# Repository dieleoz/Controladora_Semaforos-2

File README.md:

# 🚦 Controladora de Semáforos Móviles de 3 Estados (V9.1)

> 🧭 **Las decisiones vigentes viven en [`DECISIONES.md`](DECISIONES.md)** — una fila por
> decision, con su fecha, su motivo y que deroga. *(Aqui se publicaba cuantas hay; se quito el
> 11/09 porque decia 18 y 9 cuando ya eran mas: se cuentan alli.)* Si un parrafo de cualquier
> documento contradice una fila de ahi, **gana la fila**: el parrafo esta caducado. Se lee
> ANTES de encargar un cambio de alcance.

---

## 🔴 Lo que este README no puede decirte, y es lo primero

> ▶️ **Donde esta parado el trabajo y por donde se retoma lo dice [`ESTADO.md`](ESTADO.md)**, que se
> reescribe en cada cierre; aqui no se repite. Lo que paso, en [`HISTORIA.md`](HISTORIA.md) y en `git log`.

**La instalación certificada es `e303485` (V8.4, 31/07/2026).** Lo de debajo llegó a una mesa
el 3-4/09 y la noche del 04/09 —banco con dos tarjetas; la última cinta, 05/09 22:19, sobre
`42a52cd`— y 🔴 **el 10/09 llegó por primera vez a una calle: un Maestro (`SERIE:179DB0`)
corrió en El Sisga con firmware V9 `SIN_BANCO`** —el paquete del 08/09 (`7ff7d12`); después
se probó el del 10/09 (`b354fe9`)—. Su cinta y su diario están en `evidencia/` (308 tramas,
308 checksums que casan). Lo que se reportó allí, lo que dice la cinta y la rama que salió de
ahí, validada por el diff, están en `roadmap.md` §3.16 (`N-162`). 🔴 **Con `7ff7d12`, el
Maestro 179DB0 se declara en hora con el reloj parado: no se usa el Modo Degradado allí.**
**Desde el 29/09 el funcional prueba en banco las candidatas** (`a505fa2`, `6bd1e4f`, `d3606be`; cintas en
`evidencia/300920261130/`, `011020260934/`, `021020260914/`), **pero ninguna ha pasado banco completo.**

**La razon lineas de instrumento / lineas de producto la mide el pre-commit en cada commit**
(`.githooks/trinquete.sh`, contra el techo `RAZON_TECHO` de `.topes`): si sube por encima del techo, el
commit se para. El techo solo baja, cuando un acta de campo archiva un tema (`CLAUDE.md` §4). Cuenta
el indice, sin `historico/`, e incluye la app y el ESP32, asi que no se compara con las razones de la
serie anterior (esa serie, en [`HISTORIA.md`](HISTORIA.md)).

**Tres auditorías externas independientes dijeron lo mismo**, y la tercera lo dijo de la
respuesta a la segunda. La regla que salió de ahí vive en `CLAUDE.md` §0 y §8:

> **Un `20/20` sobre decenas de miles de líneas de instrumento que nunca han tocado una tarjeta
> no es un entregable: es una coartada.**

La tabla de abajo es verdad. **Lee lo que mide antes de lo que puntúa.**

---

## 📐 LA SPEC — empieza por aquí, y son nueve ficheros (`SPEC_0` a `SPEC_8`)

**Escritas el 12–13/09 desde el fuente, verificando cada afirmación contra el código; manda la SPEC y
`DECISIONES.md` es su índice.** `SPEC_0` es la vista del sistema y `SPEC_7` el modo sin reloj. Sustituyen a ~17.000
líneas de manuales que describían un sistema que ha cambiado cuatro veces.
**Nacieron por debajo de 300 líneas a propósito** (hoy `SPEC_1` y `SPEC_2` lo pasan): un fichero que no se puede leer
entero no lo lee nadie entero, y
entonces cada lector deriva su propia versión.

| | qué contesta |
|---|---|
| [`SPEC_0_El_Sistema`](05_Funcional/SPEC_0_El_Sistema.md) | la vista del sistema: qué es, cómo se pone un cruce a funcionar y lo que el equipo no hace (§5) |
| [`SPEC_7_Modo_Sin_Reloj`](05_Funcional/SPEC_7_Modo_Sin_Reloj.md) | el modo sin reloj y sin radio: el veredicto es que **no se construye** |
| [`SPEC_1_Ciclo_y_Luces`](05_Funcional/SPEC_1_Ciclo_y_Luces.md) | qué hace **un** poste con sus tres luces y su pluma: modos, tiempos, transiciones, la barrera de salidas |
| [`SPEC_2_Dos_Puntas_y_Radio`](05_Funcional/SPEC_2_Dos_Puntas_y_Radio.md) | 🔴 **lo único de verdad difícil: que los dos postes NUNCA den verde a la vez**, con una radio lenta que pierde tramas y sin cable entre ellos; y sin radio, el Degradado con testigo (§7.bis) y el **automatico a eleccion del tecnico** (§7.ter, 29/09) |
| [`SPEC_3_La_Hora`](05_Funcional/SPEC_3_La_Hora.md) | de dónde sale la hora y qué pasa cuando se pierde — **es lo que autoriza el Degradado**, o sea el modo que da verdes sin confirmar con la otra punta |
| [`SPEC_4_App_y_Bluetooth`](05_Funcional/SPEC_4_App_y_Bluetooth.md) | la **única** forma de operar el equipo (`D-16`): qué órdenes hay, qué contesta el equipo a cada una y de qué depende esa respuesta |
| [`SPEC_5_Cobre_Camaras_Pluma`](05_Funcional/SPEC_5_Cobre_Camaras_Pluma.md) | 🛑 **qué hay en cada pin, qué es peligroso y qué no se ha medido nunca.** Se lee con un destornillador en la mano |
| [`SPEC_8_Camaras_y_Barrera`](05_Funcional/SPEC_8_Camaras_y_Barrera.md) | 🛑 **qué HACE el equipo con las cámaras y la barrera**: el veto, el retardo de 3 s, cuándo pide que se revise una cámara, los dos interruptores de administrador, y **qué NO protege**. Es la otra mitad de `SPEC_5`: aquí lo que decide el **firmware**, allí lo que decide el **cobre** |
| [`SPEC_6_Campo_Radio_y_Alarmas`](05_Funcional/SPEC_6_Campo_Radio_y_Alarmas.md) | el **procedimiento de campo** del Degradado, la configuración de radio y antenas, y la tabla completa de alarmas → qué hace el técnico |

> ⚠️ **La spec dice qué HACE el equipo hoy, no qué debería hacer.** Lo que no cumple una decisión vigente vive
> en el apartado «HUECOS MEDIDOS» de cada una, con la medida pegada. **Y los manuales viejos siguen en el
> árbol a propósito**: se intentó jubilarlos y se paró con medida — hay contenido que ninguna spec cubre
> todavía (la receta de la APK, los ensayos de cámara con instrumento, la trama canónica con checksums de la
> que cuelga un pack). Está contado en `roadmap.md` 1.35(a).

## 🔧 Qué se probó en banco, y qué no

> **El 3 y 4 de Septiembre esto vio una tarjeta.** El funcional ejecutó la guía de 29 pasos
> sobre `617bd00`: **24 pasos completados**, 4 bloqueados por el enlace Bluetooth y 1 abortado
> por un incidente de seguridad. Informe en
> `evidencia/Informe_Pruebas_Banco_Semaforos_V9.0.pdf`.
>
> **Funcionó en cobre:** carga por SWD al primer intento, radio entre puntas con caída a ámbar
> en ~20 s y vuelta sola en ~3 s, talanquera, cámara de demanda y masa común a 0 V.
>
> ✅ **La regresión N-42 —el Modo Automático no movía las luces— está CERRADA EN COBRE.** La
> cerró la sesión de banco de la noche del 04/09, con el responsable delante: *«ahí cambia ese
> amarillo y este a verde. Ahora está funcionando»*. El arreglo es `ceb8cc5` —se retiró el
> asistente entero: una sola puerta, el modo arranca corriendo—. *(Este README publicó
> «regresión abierta» hasta el 07/09; el banco la había cerrado tres días antes.)*
>
> 🔴 **Y aparecieron tres defectos que ninguna cifra de la tabla de abajo podía ver**, porque
> ninguno es una propiedad del código: la tarjeta Maestro tiene un corto de 3,3 V a masa
> (**N-116**), las entradas de campo no tienen ninguna protección mientras las salidas sí
> (**N-120**), y el ESP32 no se anunciaba por Bluetooth (**N-117**). **Los tres pasaron el
> `20/20` sin despeinarlo.**
>
> *(El cuarto de aquella lista, **N-118** —«el mando A/B no responde, 0,6 V en reposo»—, quedó
> **REFUTADO el 05/09**: el propio banco había medido las dos ramas del experimento en la misma
> tabla. Mismo cobre, distinto `pinMode`, distinta tensión. Ver `05_Funcional/historico/DECISIONES_hist.md`, cerradas.)*

**Verificación actual** — cifras **copiadas del acta**
[`evidencia/2026-11-10_compuerta.txt`](evidencia/2026-11-10_compuerta.txt), que genera
`python 01_Firmware/compuerta.py` en una sola corrida. No se escriben a mano — y desde **N-62**
eso ya no es una promesa: el pack `documentos_01_cifras_del_acta` compara esta tabla contra la
última acta en cada corrida del banco. Cuando se escribió por primera vez, **falló**: esta tabla
publicaba 32 rutas y 86,4 % de flash cuando el acta que ella misma citaba medía 38 rutas y
92,8 %. Las cifras eran del 05/08 y llevaban la palabra *«copiadas»* encima.

| Comprobación | Estado | |
|---|---|---|
| guarda de rutas de los instrumentos | ✅ | 72 rutas parseadas, todas existen |
| banco por packs *(70 packs)* | 🔴 **FALLA** | **1524/1525 comprobaciones en 70 packs** — 69 PASS, **1 FALLA**. `decisiones_01_anclas` acusa a **`D-22`** (necesita una tarjeta delante); no se decora (`CLAUDE.md` §1) |
| compila Maestro / Esclavo / ESP32 | ✅ | **85.5 %** · 72.3 % · 35.8 % — *el Maestro ocupa **53420 de 62464 B** (las tres ultimas paginas quedan para la instalacion de camaras y barrera, `D-165`, las franjas de noche, `D-108`, y el testigo de `D-35`); el Esclavo, **43964 B**. Subio con los parametros de instalacion (`N-187`). Bajo al quitar la libreria RTC (`N-172`) y subio con la salida programada (`D-52`) y el verde del testigo (`D-59`)* |
| simulador funcional | ✅ | 9/9 — eran 20, y 11 de aquellas no medían nada: se retiraron una a una con su evidencia |
| compila ESP32 | ✅ | 35.8 % — 1126409 de 3.145.728 B |
| simulador del puente ESP32 | ✅ | **159/159** — las tres puntas: `bluetooth.cpp` compilado, la app en jsdom, y solo el ESP32 modelado |
| simulador de app y bluetooth | ✅ | **12/12** — estuvo en `ABORTADO` unas horas el 05/09: **N-149** le añadió el campo `ESC` al `$STATUS` y el instrumento no supo con qué compararlo. Se enseñó a leerlo el mismo día. Queda escrito porque **mientras duró, todo lo que vigilaba entró sin mirar** (`CLAUDE.md` §1) |
| **app ejecutada en DOM** | ✅ | **971/971** — carga `index.html` en jsdom, más `app.js` y **los `js/*.js` que el propio HTML declara, en su orden**, y los **ejercita**: pestañas, modales, ingesta de telemetría, *fuzzing* de 200 tramas corruptas y los botones que mandan comandos. Es el único instrumento que **ejecuta** la app en vez de leerla |
| test funcional de la app | ✅ | **71/71** — decía «22/22» a mano y ejecuta 34; su prueba de Courier RTC era una tautología |
| test unitarios TDD de la app | ✅ | **92/92** — la **segunda** suite unitaria, que hasta el 01/09 **no estaba en la compuerta**: 23 pruebas verdes que no medían nada. *(Esta fila publicó `55/55` hasta el 07/09: era la cifra del 02/09, y `documentos_01` **no la vigila** — no está en su tupla `CIFRAS`.)* |
| test unitarios de la app | ✅ | **70/70** — seis suites que no cargan el navegador: NMEA y *checksums*, generador de comandos y barrera de PIN, validación de `SET_TIEMPOS`, Courier RTC, gestor de cruces y escala de 20 cruces |
| arnés del ciclo | ✅ | **78/78** — corre sobre el `ciclo_degradado.h` real compilado, sin espejo en Python |
| arnés del respaldo | ✅ | compila el `calcularSuma()` real; identidad de `respaldo.cpp` entre puntas + prueba de vida |
| arnés del Degradado a dos puntas | ✅ | **184/184** — las dos puntas en Degradado **cada una con su reloj**. Entrega **el número**: el cruce aguanta **29 s** de desfase contra los **20,2 s** que el equipo puede acumular en 48 h, o sea factor **1,44** — y no el 2 que afirmaban los comentarios de las dos puntas |
| arnés de las dos puntas | ✅ | **204/204** — el C++ **real de las DOS puntas** en el mismo proceso y el mismo instante: verde simultáneo en **0** instantes. Cubre `G3`/`N-163` (suelta del verde), `D-34` (verde del Esclavo frente al ámbar del Maestro, `G12`–`G14`) y `D-53` (rojo+amarillo antes de cada verde). Sin banco |
| arnés del automático | ✅ | **120/120** — compila `coordinador.cpp` + `semaforo.cpp` + `modo_automatico.cpp` + `modo_inteligente.cpp`, `demanda.cpp` y el `botones.cpp` real, y comprueba SFTY-2 sobre las escrituras de pin. Las 16 nuevas son el **Bloque G de `D-33`**: el retardo de bajada de la pluma y el veto de la cámara, ejecutados |

> 🛑 **Aquí había una fila más, `arnés de pantalla`, y NO se actualiza: se RETIRA.** Compilaba los cuatro
> `lcd.cpp`/`menu.cpp` reales contra 131 `.c` de U8g2, y **se fue con el LCD** el 13/09 (`D-32` (1), `17d3a1f`).
> La compuerta baja de **20 filas a 19** y el banco pierde sus **287 comprobaciones** (145 Maestro + 142
> Esclavo): **es una bajada A PROPÓSITO, no una regresión.** Se dice aquí abajo y no en la tabla porque en la
> tabla **sólo caben filas con una medida detrás** — una fila sin medida se lee como medida.

**16 PASS · 1 FALLA · 0 ABORTADO, de 17 comprobaciones — la compuerta sale con código `1`.**

> 🔴 **El `1` es el hallazgo, no una regresión.** Lo acusa `decisiones_01_anclas`: **`D-22` está vigente en
> `DECISIONES.md` sin una línea que la construya.** `D-22` es poner `Y1` y espera **una tarjeta
> delante**: si `Y1` no oscila, el `_Error_Handler` es `noreturn` y la tarjeta queda a oscuras.
>
> 🛑 **Ninguna se apaga poniéndole un ancla:** se construye o se deja rojo. **El 07/09 se intentó cerrar las de
> entonces poniéndoles el ancla en un comentario y la compuerta se puso en `20/20` sin que se construyera nada**
> *(`roadmap.md` §3.10)*; las anclas se revirtieron y el rojo volvió, que es donde tiene que estar.

> 🟢 **Y cuando vuelva a `0`, ese verde será más peligroso que el rojo, no menos.** Mientras la
> compuerta sale con `1` nadie la confunde con un permiso; un `0` sí se confunde. Lo que dice es
> exactamente esto:
> *los modelos y los arneses de PC no encuentran nada*. **No dice que el firmware funcione en la
> tarjeta.** El contraejemplo está fechado: los tres defectos que pararon el banco del 3-4/09
> pasaron estas 19 comprobaciones sin despeinarlas. **Verde no es entregable.**

### Por qué la compuerta está hecha así — cuatro lecciones, en una línea cada una

| | |
|---|---|
| **`ABORTADO` no es `PASS`** | una comprobación que no pudo correr no dice *nada* del firmware. Así se perdió la cobertura del Maestro sin que nadie se enterara (**N-28**) |
| **Un `FALLA` contado como `PASS`** | los tres validadores monolíticos imprimían `FALLA` y salían con código `0`. Se retiraron el 05/08 exigiendo que los packs sumaran *exactamente* sus comprobaciones y que el **texto** de cada una coincidiera — Costura `41 = 41`, Maestro `64/67 = 64/67`, Esclavo `31 = 31` (**N-46**) |
| **Un `gcc` que existe no es un `gcc` que enlaza** | dos arneses cayeron a `ABORTADO` de un día para otro con el mismo compilador en el acta: `ld` no abría una ruta con `ñ`. La compuerta **le exige enlazar un `main()` vacío** antes de fiarse (**N-44**) |
| **Un pack puede estar verde sin medir nada** | la prueba 2.8 del checksum hacía `break` sobre una condición siempre cierta y no evaluaba un solo candidato. Al arreglarla apareció un camino **explotable** en `FLAGS`/`SYNC_BAJA` (**N-51**) |

**El detalle de las cuatro, con su medida, está en [`roadmap.md`](roadmap.md).**

> **Un acta no es una frase.** `evidencia/` guarda fecha, hash de HEAD y versión de toolchain de
> cada corrida, así que "20/20" deja de ser un número que envejece en un README y pasa a ser
> algo que el auditor re-corre sobre ese mismo commit. Estado de hoy en
> [`ESTADO.md`](ESTADO.md); reglas permanentes en [`CLAUDE.md`](CLAUDE.md).

### 📦 El banco son 70 packs — y eso NO es una medalla

```
python 01_Firmware/Simulaciones/banco/correr.py --listar
python 01_Firmware/Simulaciones/banco/correr.py --pack esclavo_03   # un fallo, solo, en 1 s
```

**Por qué se migró** — había tanto instrumento como firmware: **8.898 líneas contra 8.895, uno a
uno**. Y los simuladores no ejecutan el C++, lo *reimplementan a mano*: son una segunda copia que
alguien sincroniza, y eso falló cuatro veces en una semana.

⚠️ **Pero `correr.py` NO es `compuerta.py`.** El banco es **una fila de veinte**: un
`x/y` de packs no dice nada de las otras diecinueve, y una de ellas puede estar en `ABORTADO` por
el mismo cambio que acabas de comitear. **Antes de comitear se corre `compuerta.py`, completo.**

### 📦 Qué se le manda al funcional, y por qué son dos paquetes

**Un paquete es una autorización implícita:** quien lo recibe asume que puede instalarlo. Con el
banco sin pasar, eso obliga a separar lo que pide una medida de lo que entrega una versión.

| | |
|---|---|
| **Encargo de banco** | Pide que alguien ponga la tarjeta delante. Lleva los binarios con sus MD5 y los firmware marcados `SIN_VALIDAR` en el propio nombre |
| **Entrega de versión** | Fuente para PlatformIO + APK + el `.html` de pruebas vigente + `LEEME_PRIMERO.txt`. **Sin `.bin`, sin manuales, sin `.md` y sin acta**; se deja en `entregas/` (ignorada por git), nunca en la raíz |

El `LEEME_PRIMERO` **no abre con la cifra en verde** — abre diciendo qué corre en campo, que esto
no es eso, y qué sigue roto. El método está en `orquestador:entregar` y en
`.claude/particularidades/entregar.md`.

**Certificado en campo:** 31 de Julio de 2026 *(V8.4, dos radios en enlace directo)*
**Última actualización del repositorio:** 11 de Septiembre de 2026 *(la cifra vigente y su hash de
HEAD están en el acta que cita la tabla de arriba, y no se repiten aquí: este pie llevaba
`14 PASS` sobre HEAD `2cde016` cuando el acta ya medía otra cosa, y un recuento viejo no se lee
como viejo, se lee como medida.)*
**Repositorio Oficial:** [`github.com/dieleoz/Controladora_Semaforos-2`](https://github.com/dieleoz/Controladora_Semaforos-2.git) — remoto `origin`.
**Normativa Aplicable:** Resolución 2024 del Ministerio de Transporte de Colombia (Secuencia de Luces y Tiempos de Seguridad Vial)

---

## 🧭 La arquitectura vigente, decidida en obra el 28/08 y cerrada el 31/08

**El documento con el detalle medido —`fichero:linea` en cada afirmación, las decisiones
abiertas con dueño y las medidas de multímetro— es
[`05_Funcional/17_Arquitectura_28-08_y_Decisiones_Abiertas.md`](05_Funcional/17_Arquitectura_28-08_y_Decisiones_Abiertas.md),
y manda la SPEC (`05_Funcional/SPEC_0..8`; [`DECISIONES.md`](DECISIONES.md) es su índice). Aquí va sólo el reparto,
porque un README que describe el aparato anterior manda a cablear el aparato anterior.**

### El reparto, en una frase

**El STM32 sigue siendo el controlador del semáforo. El ESP32 es un módulo de expansión colgado de
un puerto serie: aporta reloj y Bluetooth, y NO manda sobre las luces.**

```
                       fuente propia 12 V (NO sale de la tarjeta)
                                    |
   +--------------------+     +-----v--------------------+
   |   STM32F103C8      |     |         ESP32            |
   |   (controlador)    |     |   (modulo de expansion)  |
   |                    |     |                          |
   |  luces    J3-J8    |     |  DS3231  GPIO21 SDA      |
   |  barrera  J15      |     |          GPIO22 SCL      |
   |  camaras  J16 (*)  |     |          (pila propia)   |
   |  LoRa     J12      |     |                          |
   |           USART3   |     |  Bluetooth (sustituye    |
   |                    |     |   al modulo SPP)         |
   |  USART1 remapeado  |     |                          |
   |  PB6 TX == J17 p3 <------ GPIO16 (RX2)              |
   |  PB7 RX == J17 p2 ------> GPIO17 (TX2)              |
   +---------|----------+     +-----------|--------------+
             |                            |
             +-------- masa comun --------+
                       9600 8N1
```

*(\*) Aquí ponía ~~`camaras J14, J16`~~. ✏️ **11/09:** las cámaras van a `J16` —dos por poste, p10 y
p12 (`D-25`)—. `J14` no lleva cámara: ~~`A-2` lo reserva al fin de carrera,~~ **pero el firmware lo sigue
leyendo como cámara de demanda (`CAM_DEMANDA_PIN` = `PB0`)** — ~~conflicto abierto, del responsable~~
→ **`D-27` (11/09): `J14` LIBRE, sin cablear; el fin de carrera no se instala en este despliegue**,
así que en `J14` no se conecta nada (`ARQUITECTURA.map` §7.3).*

### El enlace, pin a pin — y la fuente

| ESP32 | dirección | `J17` | STM32 |
|---|---|---|---|
| `GPIO17` (TX2) | ➡️ | **p2** | `PB7` — **RX** del micro |
| `GPIO16` (RX2) | ⬅️ | **p3** | `PB6` — **TX** del micro |
| `GND` | — | p7 o p9 | `GND` — **masa común obligatoria** |

`9600 8N1`. El `USART1` ya está remapeado a `PB6`/`PB7` en el firmware de las dos puntas (N-76,
`bluetooth.cpp`, `grep -n "SerialBT(PB7, PB6)"`) — el puerto y el pinout son los mismos que ya
tenía el módulo SPP; **lo que se enchufa, no**.

> 🔴 **El ESP32 lleva fuente propia desde 12 V. NO cuelga de los 3,3 V de `J17` p6/p8.** Ese riel
> sale del `U5` y es **el mismo que alimenta al STM32 que gobierna el semáforo**: un ESP32 con radio
> da picos de corriente del orden de medio amperio, y un reset del controlador provocado por un
> periférico de diagnóstico es el reparto de riesgo que no se acepta. **El accesorio no puede tumbar
> al que manda.**

### Lo que se retira, y por qué — tachado, no borrado

> **Una vía descartada que desaparece en silencio vuelve a proponerse.** Por eso van tachadas con su
> motivo al lado, y no suprimidas.

| se retira | por qué | consecuencia |
|---|---|---|
| ~~**Pantalla LCD ST7920** (las dos puntas)~~ | **este PCB no permite ampliación**, y la pantalla ocupaba cinco pines —`PB3` `PB4` `PB5` `PB6` `PB7`— de los que el Bluetooth necesita `PB6`/`PB7`: **no había de dónde sacarlos**. Confirmado por el responsable el 05/09 (`D-17.bis`) | toda la operación pasa por la app. **Se retira del EQUIPO, no del código**: `lcd.cpp` y `menu.cpp` siguen compilando y `Validacion_LCD` sigue dando `271/271` sobre un framebuffer del PC |
| ~~**Módulo Bluetooth SPP dedicado** (`HC-05` / `JDY-30`)~~ | lo sustituye el ESP32 por el mismo `J17` | **no se compran** |
| ~~**Los CUATRO botones**~~ | los pines 3 y 4 son los que necesitan las cámaras, y el 05/09 el responsable retiró la botonera entera: **«todo por app»** | ⚠️ **DOS funciones de botón están muertas y DOS SIGUEN VIVAS, y el reparto no es casual**: `botonAceptar()`/`botonCancelar()` son `return false;` —son los de `PB14`/`PB15`, **los pines que ahora son cámaras**—; pero `botonArriba()`/`botonAbajo()` tienen llamadores vivos y leen `BOTON1`/`BOTON2`, **que son los pines del mando**. 🔴 **Lo que alguien cierre en `J16` p5/p8 contra los 3,3 V SIGUE ENTRANDO al firmware.** *(`Botón 1` y `Botón 2` SON `Mando A` y `Mando B`: los mismos dos pines con dos nombres.)* |
| **El mando de relés** (hardware) | 05/09, el responsable: *«ya no tenemos mandos de A y B, sólo la app»* (`D-1`) | Software retirado por `D-30` (12/09; *«hasta el sw lo quitamos»*): **`mando.cpp` salió de las dos puntas en `f57a401` (14/09)**. `J16` p5/p8 siguen vacíos y no se cablean (`D-44`, `CLAUDE.md` §3) |

> 🔴 **Y su consecuencia declarada, que es una propiedad del sistema y no una avería (`D-16`):
> SIN TELÉFONO NO HAY FORMA DE OPERAR EL EQUIPO.** Ni ámbar, ni volver a automático, ni parar el
> cruce. Va escrito en el manual del operario: el teléfono es herramienta crítica.

### Las cámaras van a `J16` p10 y p12 — **dos por poste** (`D-25`, 11/09) — y **ya se cablean**

*(Resumen: la tabla que manda es `05_Funcional/17_…` §1.7. La columna «red» es el nombre heredado
del netlist, **no el papel del pin**.)*

| `J16` | red | pin | uso nuevo |
|---|---|---|---|
| p1 | `/12V` | — | 🔴 **12 V crudos. Se tapa físicamente en CADA equipo que se monte** (N-120) — es el único conector de señal de la tarjeta que los trae, sin opto ni clamp |
| p5 | `/Boton1` | `PB9` | **libre y SIN CABLEAR** (`A-2`, cerrada el 05/09: ~~el fin de carrera va a `J14`~~ — *11/09, `D-27`: y tampoco allí, el fin de carrera no se instala; `J14` queda libre*). 🔴 **El firmware sigue leyendo ese pin** y alimentando el reconocedor de secuencias del mando |
| p8 | `/Boton2` | `PB13` | igual que p5 |
| p10 | `/Boton3` | `PB14` | 🎯 **`CAM_C_PIN` — cámara 1**, contacto de alarma entre p9 (3,3 V) y p10 *(verificada en banco el 03/09)* |
| p12 | `/Boton4` | `PB15` | 🎯 **`CAM_D_PIN` — cámara 2**, contacto de alarma entre p11 (3,3 V) y p12 |

> ✅ **`D-25` (11/09, el responsable): las conexiones de la guía de cámaras del Sisga quedan
> DEFINITIVAS** —4 cámaras, dos por poste— y derogan de `D-13` solo *«una por poste, p12 vacío»*.
> 🔴 **Lo que el que cablea tiene que saber, medido en el firmware de hoy:** las **dos entradas hacen
> LO MISMO** (piden paso; `botones.cpp`, `CAM_J16[2]`); desde el 14/09 **retienen la bajada de la pluma** (`D-33`,
> `363e375`, `SPEC_8` §1), y **una segunda cámara muerta desde la instalación no la detecta nadie**
> (el vigilante salta el pin que nunca dio un flanco): se comprueba cada cámara por separado al
> instalar. Las frases falsas de la guía del 10/09 se corrigen en su versión nueva (`roadmap.md` §3.16)
> → ✏️ **11/09: es [`05_Funcional/Camaras_Sisga_4x.html`](05_Funcional/Camaras_Sisga_4x.html)**, con
> la fe de erratas delante y la talanquera en `J15` al final. ⚠️ **La app** (también la APK del 10/09)
> **pone `CAM: OK — las dos ven` en cuanto detecta CUALQUIERA de las dos cámaras del poste**, aunque la
> otra no haya detectado nunca: por eso **cada cámara se comprueba con el multímetro en su borne**
> (0 V en reposo, 3,3 V con algo en la zona), y no con la app.

> ✅ **La medida `M3` está CERRADA desde el 03/09 y las cámaras se cablean** (`D-3`). Medido en
> cobre —multímetro, conector vacío, paso 20 de la Guía—: el pull-down de **10 kΩ** que declaraba
> el netlist **es real y está en las cuatro posiciones** (`R65`–`R68` con su 100 nF); `p10` y `p12`
> dan **0 V en reposo**, así que la entrada es **activa en ALTO**, que es lo que el firmware ya
> hacía. El paso 21 cableó `p10` contra `p11` en normalmente abierto y funcionó, **sin demandas
> fantasma**.
>
> ~~🛑 No se cablea cámara a `J16` hasta cerrar la medida `M3`~~ — **caducado**: este README lo
> siguió publicando cuatro días después de cerrarse, y el 05/09 se le contestó al responsable con
> ese párrafo. Se conserva tachado porque una vía descartada que desaparece vuelve a proponerse.

> ⚠️ **El orden sigue siendo asimétrico: primero el firmware cargado, después el destornillador.**
> Un commit no protege de un destornillador — se exige la **carga verificada en la tarjeta**, no el
> merge. ✏️ **11/09, con `D-25` vale para los DOS pines:** con un binario anterior a `deeeab4` (la
> V8.4 incluida) `PB14` es `botonAceptar()` y **`PB15` es `botonCancelar()`**, así que lo que se
> cablee en `p10` **o en `p12`** puede actuar como un botón en un equipo que está en la calle.

### Seis luces gobernadas, no ocho

`pines.h` declara ocho salidas de luz, pero **el semáforo peatonal nunca se conectó a nada**:

| declarado | pin | ¿lo escribe alguien? |
|---|---|---|
| `ROJO1` `AMARILLO1` `VERDE1` / `ROJO2` `AMARILLO2` `VERDE2` | `PA0`-`PA5` | ✅ sí, y **sólo** `semaforo.cpp` |
| `ROJO_PEATON` · `VERDE_PEATON` | `PA6` · `PA7` | 🔴 **ni un `pinMode` ni un `digitalWrite` en ninguna de las dos puntas** |
| `BUZZER` | `PB1` | 🔴 **igual: declarado y nunca escrito** |

Es **hardware pagado y muerto** —tiene opto, MOSFET y bornera propia—. Se anota aquí porque
*"conserva las 8 luces"* es la clase de frase que se copia de documento en documento sin que nadie
corra el `grep`: **la barrera de salidas de `CLAUDE.md` §2 custodia ocho nombres; el equipo mueve
seis.**

### 🛑 Lo que esta arquitectura NO autoriza

- **Nada de esto ha pasado banco entero, y la compuerta no lo suple.** Lo que este apartado llama
  medido se midió en su mayoría **sobre ficheros** —el `.cpp`, el `.h`, el `.kicad_sch` y el
  `.kicad_pcb`—. Un fichero dice lo que alguien dibujó; una placa dice lo que se fabricó.
- 🟠 **Sin pantalla, `$STATUS` es el único tablero que existe** — y hoy trae `BAT:--` porque
  **no hay un solo `analogRead` en `src/`**. Un campo que no se mide se retira o se marca; no se
  deja con aspecto de medida.

**El plano de conexiones que se entrega —`J17`, `J16`, `PB6`/`PB7`, el `DS3231` y el SWD— es
[`05_Funcional/Montaje_Campo_2026-10-05.html`](05_Funcional/Montaje_Campo_2026-10-05.html)**,
con el cobre medido en `17_...` y SPEC_5.

---

## 🗂️ Paquete Oficial de Entregables y Manuales (`05_Funcional/`, en `.md` y `.docx`)

> **ARCHIVADOS el 28/09 en `05_Funcional/historico/`: todas las filas salvo la 10 y la 17.** No son vigentes;
> mandan las `SPEC_0..8` (CLAUDE.md §15). La columna «Estado» describe cada manual antes de archivarlo.

| # | Manual | Estado |
|---|---|---|
| 1 | [`1_Manual_Usuario`](05_Funcional/historico/1_Manual_Usuario.md) | Operación y comportamiento vial (Resolución 2024) |
| 2 | [`2_Manual_Hardware_y_Pruebas`](05_Funcional/historico/2_Manual_Hardware_y_Pruebas.md) | Hardware, borneras y ensamblaje STM32 |
| 3 | [`3_Protocolo_Pruebas_Rigurosas`](05_Funcional/historico/3_Protocolo_Pruebas_Rigurosas.md) | Protocolo de auditoría funcional. ⚠️ **reescrito**: cada prueba lleva su marca `SE REESCRIBE` / `SE RETIRA` / `SE APLAZA` |
| 4 | [`4_Manual_Configuracion_Radios`](05_Funcional/historico/4_Manual_Configuracion_Radios.md) | E90-DTU (2.4 kbps / 30 dBm / FEC) |
| 5 | [`5_Manual_Puente_ESP32`](05_Funcional/historico/5_Manual_Puente_ESP32.md) | Puente repetidor V7.6 — **retirado** (`D-157`) |
| 6 | [`6_Preguntas_Diseno_Funcional`](05_Funcional/historico/6_Preguntas_Diseno_Funcional.md) | Decisiones de diseño cerradas |
| 7 | [`7_Especificacion_Antenas`](05_Funcional/historico/7_Especificacion_Antenas.md) | Antenas y línea de vista |
| 8 | [`8_Procedimiento_Modo_Degradado`](05_Funcional/historico/8_Procedimiento_Modo_Degradado.md) | Operación de emergencia por reloj sin radio |
| 9 | [`9_Manual_Parametrizacion_Camara_IA`](05_Funcional/historico/9_Manual_Parametrizacion_Camara_IA.md) | **4 cámaras, dos por poste** en `J16` p10/p12 (`D-25`, 11/09) — ~~⚠️ **el manual todavía dice una por poste: pendiente de alinear**~~ ✏️ **alineado el 11/09** (el `.docx` no: se regenera aparte). **Es el entregable principal del diseño de cámaras** (`D-12`): toda la inteligencia vive en la configuración de la cámara. 🎯 |
|  |  | **11/09, `D-27`: sus VALORES de configuración salen del manual del modelo, [`05_Funcional/historico/MANUAL_CONFIGURACION_CAMARAS_IA.md`](05_Funcional/historico/MANUAL_CONFIGURACION_CAMARAS_IA.md) §4** —tabla valor a valor en su §4 Paso 3—; las cuatro cámaras están compradas |
| 10 | [`10_Manual_Modulo_Bluetooth_Telemetria`](05_Funcional/historico/10_Manual_Modulo_Bluetooth_Telemetria.md) | ⚠️ **manda enchufar un `HC-05` en `J17`, que es donde va el ESP32** |
| 11 | [`11_Manual_Instalacion_RTC_DS3231_Bateria`](05_Funcional/historico/11_Manual_Instalacion_RTC_DS3231_Bateria.md) | ~~`DS3231` en `PB0`/`PB8`~~ → **se muda al ESP32**. ⚠️ **manual sin corregir** |
| 12 | [`12_Cobertura_de_Pruebas_y_Huecos`](05_Funcional/historico/12_Cobertura_de_Pruebas_y_Huecos.md) | Qué mide cada instrumento y **qué queda sin medir** |
| 13 | [`13_Manual_Modulo_Expansion_I2C_y_Compras`](05_Funcional/historico/13_Manual_Modulo_Expansion_I2C_y_Compras.md) | ⚠️ **su §4 queda sin sujeto**: el I²C ya no vive en el STM32 |
| 14 | [`14_Manual_App_Movil_IOT_VIAL`](05_Funcional/historico/14_Manual_App_Movil_IOT_VIAL.md) | Operación de la app: SPP, gestor de cruces y Courier RTC |
| 15 | [`15_Lista_de_Compras_Hardware`](05_Funcional/historico/15_Lista_de_Compras_Hardware.md) | **Qué se pide, cuánto y cuándo** |
| 16 | [`16_Documento_Auditoria_Arquitectura_y_Usabilidad_App`](05_Funcional/historico/16_Documento_Auditoria_Arquitectura_y_Usabilidad_App_IOT_VIAL.md) | Auditoría de arquitectura y usabilidad de la app |
| 17 | [`17_Arquitectura_28-08_y_Decisiones_Abiertas`](05_Funcional/17_Arquitectura_28-08_y_Decisiones_Abiertas.md) | 🧭 **Manda sobre las filas 9, 10, 11 y 13.** Es donde se anotan las medidas de cobre |
| 18 | [`18_Especificacion_Firmware_ESP32`](05_Funcional/historico/18_Especificacion_Firmware_ESP32.md) | Especificación del firmware del módulo de expansión ESP32 |
| 19 | [`19_Especificacion_Placa_Portadora_ESP32`](05_Funcional/historico/19_Especificacion_Placa_Portadora_ESP32.md) | Especificación de la placa portadora del ESP32 |

*(**La lista se ha desfasado CUATRO veces por lo mismo, y sigue sin instrumento**: el 27/08 anunciaba
11 manuales de los 14 que existían; el 28/08, 15 de 16; el 31/08, 16 de 17; y hasta el 11/09, 17 de
**19**. Contar los ficheros es `ls 05_Funcional/[0-9]*.md`; que nadie lo haga es lo que hace falta
cerrar.)*

---

## 🛠️ Estructura del Ecosistema de Firmware

- [`01_Firmware/Maestro`](01_Firmware/Maestro): **El controlador.** Máquina de estados STM32,
  barrera de salidas (`semaforo.cpp`, el único que escribe pines de luz), Modo Degradado, mando de
  relés (código conservado) y telemetría Bluetooth (`USART1` **remapeado a `PB6`/`PB7` → `J17`**).
- [`01_Firmware/Esclavo`](01_Firmware/Esclavo): Nodo secundario STM32 con ACK por radio
  (`USART3`), fallback de orfandad a **25 s**, ámbar local con veto SFTY-21 y telemetría
  Bluetooth.
- [`01_Firmware/ESP32_Expansion`](01_Firmware/ESP32_Expansion): El módulo de expansión —reloj
  `DS3231` y Bluetooth—, **con watchdog** (`vigilante.cpp`).
- [`01_Firmware/historico/Repetidor`](01_Firmware/historico/Repetidor): el puente ESP32 de radio, **retirado**
  (`D-157`): la arquitectura es de dos radios en enlace directo. No se compila ni se empaqueta.
- [`01_Firmware/Simulaciones/`](01_Firmware/Simulaciones): simuladores y `banco/` con sus
  packs *(cuántos, en el acta)*.
- [`01_Firmware/Validacion_LCD/`](01_Firmware/Validacion_LCD) · `_Ciclo/` · `_Respaldo/` ·
  `_Automatico/`: los arneses que compilan C++ real. Qué compila cada uno y su punto ciego:
  [`ARQUITECTURA.map`](ARQUITECTURA.map); su crónica,
  [`ARQUITECTURA_hist.map`](05_Funcional/historico/ARQUITECTURA_hist.map).
- [`01_Firmware/compuerta.py`](01_Firmware/compuerta.py): **la única forma correcta de
  verificar** — `16 PASS · 1 FALLA · 0 ABORTADO`, exit code 1. Las cifras están en la tabla de
  arriba, que se copia del acta; ésta es sólo la puerta. Qué se corre según lo que se toca (la
  cadencia) y por qué el simulador está congelado: `CLAUDE.md` §4.
- [`.githooks/`](.githooks) y [`.topes`](.topes): el pre-commit del método (topes de documentos,
  ancho, relatos, 500 líneas por fichero de código salvo el firmware grabado) y el trinquete
  instrumentos/producto. Se activa con `git config core.hooksPath .githooks`.
- [`.claude/particularidades/`](.claude/particularidades): lo propio de este repo para las skills
  del plugin `orquestador@diego` (`entregar`, `verificar`) y la mecánica larga de `CLAUDE.md`.
- `ESTADO.md` es el punto de retomar; `HISTORIA.md`, la crónica; `DECISIONES.md`, lo ya contestado.
- **Los paquetes no se versionan:** salen a `entregas/` (ignorada por git), y los retirados a
  `entregas/RETIRADOS/`.

> 🛑 **Y para cerrar donde se abrió: nada de este README es un permiso.** En campo corre la
> **V8.4**; la V9.1 compila y **pasa 18 de las 19 filas de la compuerta — la que falla es el censo de decisiones sin construir, y falla con razón** (`D-22` necesita una tarjeta delante). **Lo que hay hoy en el árbol no ha visto una
> tarjeta**. **Nada sube a campo sin pasar banco** — y el banco no lo sustituye ningún número verde
> de esta página.

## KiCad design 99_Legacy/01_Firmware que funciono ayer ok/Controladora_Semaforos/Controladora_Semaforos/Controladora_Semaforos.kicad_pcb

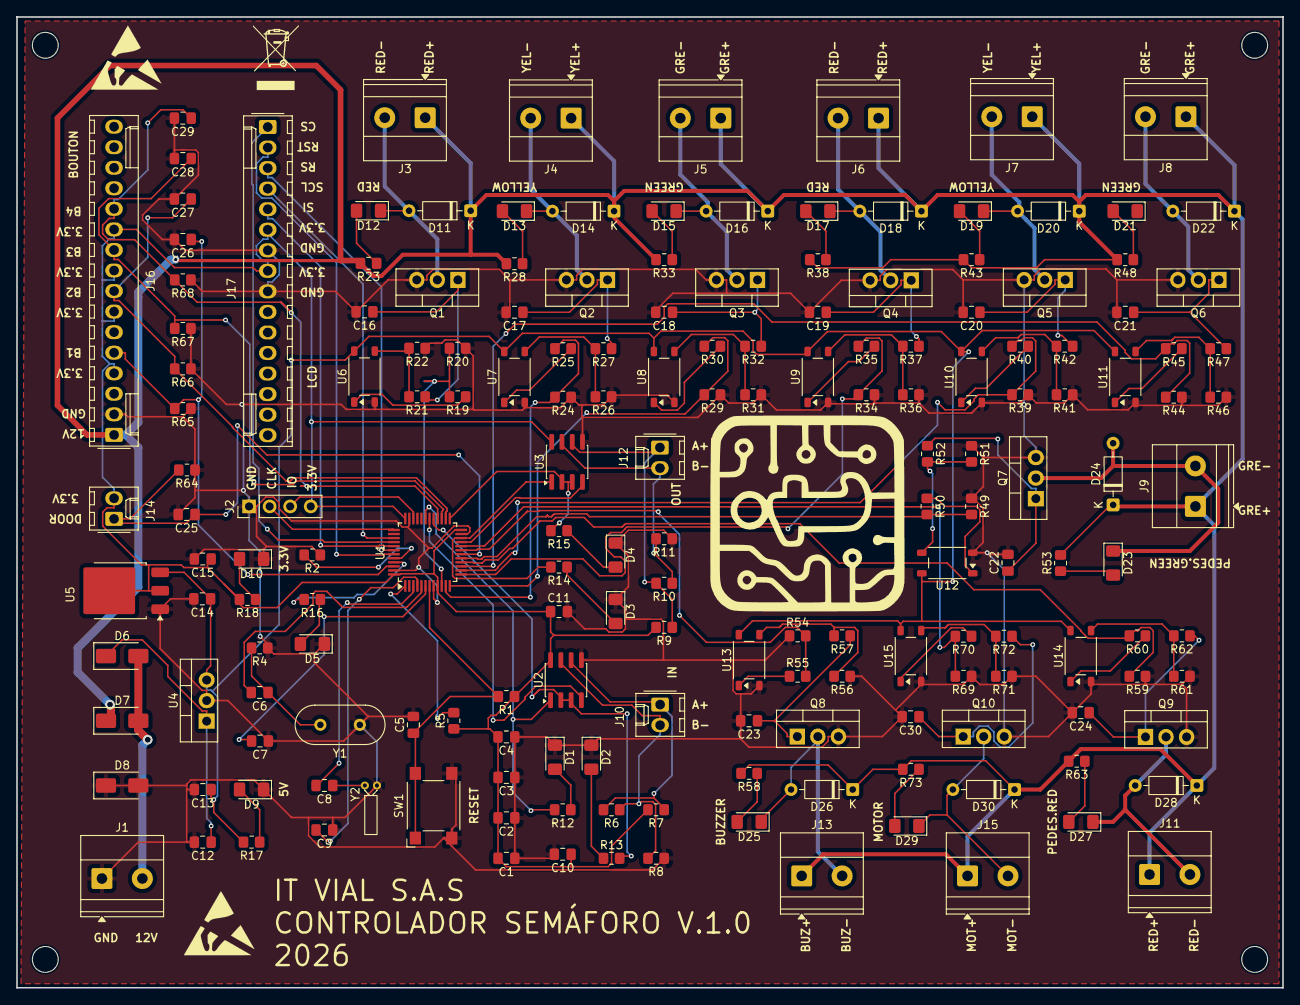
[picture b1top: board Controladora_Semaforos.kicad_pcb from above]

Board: 2 copper layers, 156.5 x 120.0 mm, 184 parts (0 on the bottom side), 105 nets.

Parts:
C1, C2, C3, C4, C10, C11: 100 nF; C_0805_2012Metric_Pad1.18x1.45mm_HandSolder
C5: 1 uF; C_0805_2012Metric_Pad1.18x1.45mm_HandSolder
C6, C7, C8, C9: 20 pF; C_0805_2012Metric_Pad1.18x1.45mm_HandSolder
C12, C13, C14, C15: 10uF; C_0805_2012Metric_Pad1.18x1.45mm_HandSolder
C16, C17, C18, C19, C20, C21, C22, C23, C24, C30: 100nF; C_0805_2012Metric_Pad1.18x1.45mm_HandSolder
C25, C26, C27, C28, C29: 100nf; C_0805_2012Metric_Pad1.18x1.45mm_HandSolder
D1, D2, D3, D4, D5, D9, D10, D12, D13, D15, D17, D19, D21, D23, D25, D27, D29: LED; LED_1206_3216Metric_Pad1.42x1.75mm_HandSolder
D6, D7, D8: SS210; D_SMA
D11, D14, D16, D18, D20, D22, D24, D26, D28, D30: 1N4148; D_DO-35_SOD27_P7.62mm_Horizontal
H1, H2, H3, H4: MountingHole_3.2mm_M3_DIN965
J1, J3, J4, J5, J6, J7, J8, J9, J11, J13, J15: Conn_01x02; TerminalBlock_Phoenix_MKDS-1,5-2_1x02_P5.00mm_Horizontal
J2: Conn_01x04_Pin; PinHeader_1x04_P2.54mm_Vertical
J10, J12, J14: Conn_01x02; Molex_KK-254_AE-6410-02A_1x02_P2.54mm_Vertical
J16: Conn_01x12_Pin; Molex_KK-254_AE-6410-16A_1x16_P2.54mm_Vertical
J17: Conn_01x13_Pin; Molex_KK-254_AE-6410-16A_1x16_P2.54mm_Vertical
Q1, Q2, Q3, Q4, Q5, Q6, Q7, Q8, Q9, Q10: IRLZ44N; TO-220-3_Vertical
R1, R20, R22, R24, R26, R29, R31, R34, R36, R39, R41, R44, R46, R49, R51, R54, R56, R59, R61, R64, R65, R66, R67, R68, R69, R71: 10K; R_0805_2012Metric_Pad1.20x1.40mm_HandSolder
R2: 10k; R_0805_2012Metric_Pad1.20x1.40mm_HandSolder
R4: 1M; R_0805_2012Metric_Pad1.20x1.40mm_HandSolder
R5: 0; R_0805_2012Metric_Pad1.20x1.40mm_HandSolder
R6, R10: 120; R_0805_2012Metric_Pad1.20x1.40mm_HandSolder
R7, R8, R9, R11: 4.7K; R_0805_2012Metric_Pad1.20x1.40mm_HandSolder
R12, R13, R14, R15, R16, R17, R23, R28, R33, R38, R43, R48, R53, R58, R63, R73: 1K; R_0805_2012Metric_Pad1.20x1.40mm_HandSolder
R18: 330; R_0805_2012Metric_Pad1.20x1.40mm_HandSolder
R19, R21, R25, R27, R30, R32, R35, R37, R40, R42, R45, R47, R50, R52, R55, R57, R60, R62, R70, R72: 220; R_0805_2012Metric_Pad1.20x1.40mm_HandSolder
SW1: SW_Omron_B3FS; SW_SPST_Omron_B3FS-100xP
U1: STM32F103C8Tx; LQFP-48_7x7mm_P0.5mm
U2, U3: MAX3485; SOIC-8_3.9x4.9mm_P1.27mm
U4: LM7805_TO220; TO-220-3_Vertical
U5: LM1117DT-3.3; TO-252-3_TabPin2
U6, U7, U8, U9, U10, U11, U12, U13, U14, U15: TLP127; Toshiba_SOIC-4-6_4.4x3.6mm_P1.27mm
V1, V2: ESD-Logo_8.9x8mm_SilkScreen
V3: WEEE-Logo_5.6x8mm_SilkScreen
Y1: 8MHz; Crystal_HC49-U_Vertical
Y2: 32.768kHz; Crystal_DS10_D1.0mm_L4.3mm_Horizontal

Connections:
/3.3V: C1.2, C2.2, C3.2, C4.2, C10.1, C11.1, C15.1, J2.4, J14.2, J16.4, J16.7, J16.9, J16.11, J17.6, J17.8, R1.1, R5.1, R7.2, R9.2, R18.2, U1.9 (VDDA), U1.24 (VDD), U1.36 (VDD), U1.48 (VDD), U2.8 (VCC), U3.8 (VCC), U5.2 (VO)
/5V: C13.1, C14.1, R17.2, U4.3 (VO), U5.3 (VI), U6.6, U7.6, U8.6, U9.6, U10.6, U11.6, U12.6, U13.6, U14.6, U15.6
/12V: D7.1 (K), D11.1 (K), D14.1 (K), D16.1 (K), D18.1 (K), D20.1 (K), D22.1 (K), D24.1 (K), D26.1 (K), D28.1 (K), D30.1 (K), J3.1, J4.1, J5.1, J6.1, J7.1, J8.1, J9.1, J11.1, J13.1, J15.1, J16.1, R23.2, R28.2, R33.2, R38.2, R43.2, R48.2, R53.2, R58.2, R63.2, R73.2
/Boton1: C26.1, J16.5, R65.2, U1.46 (PB9)
/Boton2: C27.1, J16.8, R66.2, U1.26 (PB13)
/Boton3: C28.1, J16.10, R67.2, U1.27 (PB14)
/Boton4: C29.1, J16.12, R68.2, U1.28 (PB15)
/Buzzer: R54.2, R55.2, U1.19 (PB1)
/CS: J17.1, U1.40 (PB4)
/Motor: R69.2, R70.2, U1.20 (PB2)
/PA8: R13.2, U1.29 (PA8), U2.2 (~RE), U2.3 (DE)
/PA9: U1.30 (PA9), U2.4 (DI)
/PA10: R12.2, U1.31 (PA10), U2.1 (RO)
/PB8: R16.2, U1.45 (PB8)
/PB10: U1.21 (PB10), U3.4 (DI)
/PB11: R14.2, U1.22 (PB11), U3.1 (RO)
/PB12: R15.2, U1.25 (PB12), U3.2 (~RE), U3.3 (DE)
/Puerta: C25.1, J14.1, R64.2, U1.18 (PB0)
/RS(A0): J17.3, U1.42 (PB6)
/RST: J17.2, U1.43 (PB7)
/S1: R19.2, R20.2, U1.10 (PA0)
/S2: R24.2, R25.2, U1.11 (PA1)
/S3: R29.2, R30.2, U1.12 (PA2)
/S4: R34.2, R35.2, U1.13 (PA3)
/S5: R39.2, R40.2, U1.14 (PA4)
/S6: R44.2, R45.2, U1.15 (PA5)
/S7: R59.2, R60.2, U1.16 (PA6)
/S8: R49.2, R50.2, U1.17 (PA7)
/SCL: J17.4, U1.39 (PB3)
/SI: J17.5, U1.41 (PB5)
GND: C1.1, C2.1, C3.1, C4.1, C5.2, C7.1, C9.1, C10.2, C11.2, C12.2, C13.2, C14.2, C15.2, C16.2, C17.2, C18.2, C19.2, C20.2, C21.2, C22.2, C23.2, C24.2, C25.2, C26.2, C27.2, C28.2, C29.2, C30.2, D1.1 (K), D2.1 (K), D3.1 (K), D4.1 (K), D5.1 (K), D8.1 (K), D8.2 (A), D9.1 (K), D10.1 (K), J1.1, J2.1, J16.2, J17.7, J17.9, Q1.3 (S), Q2.3 (S), Q3.3 (S), Q4.3 (S), Q5.3 (S), Q6.3 (S), Q7.3 (S), Q8.3 (S), Q9.3 (S), Q10.3 (S), R2.1, R4.1, R8.1, R11.1, R20.1, R22.1, R24.1, R26.1, R29.1, R31.1, R34.1, R36.1, R39.1, R41.1, R44.1, R46.1, R49.1, R51.1, R54.1, R56.1, R59.1, R61.1, R64.1, R65.1, R66.1, R67.1, R68.1, R69.1, R71.1, SW1.2, U1.8 (VSSA), U1.23 (VSS), U1.35 (VSS), U1.47 (VSS), U2.5 (GND), U3.5 (GND), U4.2 (GND), U5.1 (GND), U6.3, U7.3, U8.3, U9.3, U10.3, U11.3, U12.3, U13.3, U14.3, U15.3, Y1.1, Y2.2
unnamed: C6.1, R4.2, Y1.2
unnamed: C8.1, Y2.1
unnamed: D1.2 (A), R12.1
unnamed: D2.2 (A), R13.1
unnamed: D3.2 (A), R14.1
unnamed: D4.2 (A), R15.1
unnamed: D5.2 (A), R16.1
unnamed: D6.2 (A), D7.2 (A), J1.2
unnamed: C12.1, D6.1 (K), U4.1 (VI)
unnamed: D9.2 (A), R17.1
unnamed: D10.2 (A), R18.1
unnamed: D11.2 (A), D12.1 (K), J3.2, Q1.2 (D)
unnamed: D12.2 (A), R23.1
unnamed: D13.2 (A), R28.1
unnamed: D13.1 (K), D14.2 (A), J4.2, Q2.2 (D)
unnamed: D15.2 (A), R33.1
unnamed: D15.1 (K), D16.2 (A), J5.2, Q3.2 (D)
unnamed: D17.2 (A), R38.1
unnamed: D17.1 (K), D18.2 (A), J6.2, Q4.2 (D)
unnamed: D19.2 (A), R43.1
unnamed: D19.1 (K), D20.2 (A), J7.2, Q5.2 (D)
unnamed: D21.2 (A), R48.1
unnamed: D22.2 (A), J8.2, Q6.2 (D)
unnamed: D23.2 (A), R53.1
unnamed: D23.1 (K), D24.2 (A), J9.2, Q7.2 (D)
unnamed: D25.2 (A), R58.1
unnamed: D25.1 (K), D26.2 (A), J13.2, Q8.2 (D)
unnamed: D27.2 (A), R63.1
unnamed: D27.1 (K), D28.2 (A), J11.2, Q9.2 (D)
unnamed: D29.2 (A), R73.1
unnamed: D29.1 (K), D30.2 (A), J15.2, Q10.2 (D)
unnamed: J2.2, U1.37 (PA14)
unnamed: J2.3, U1.34 (PA13)
unnamed: J10.1, R6.2, R7.1, U2.6 (A)
unnamed: J10.2, R6.1, R8.2, U2.7 (B)
unnamed: J12.1, R9.1, R10.2, U3.6 (A)
unnamed: J12.2, R10.1, R11.2, U3.7 (B)
unnamed: C16.1, Q1.1 (G), R21.1
unnamed: C17.1, Q2.1 (G), R27.1
unnamed: C18.1, Q3.1 (G), R32.1
unnamed: C19.1, Q4.1 (G), R37.1
unnamed: C20.1, Q5.1 (G), R42.1
unnamed: C21.1, Q6.1 (G), R47.1
unnamed: C22.1, Q7.1 (G), R52.1
unnamed: C23.1, Q8.1 (G), R57.1
unnamed: C24.1, Q9.1 (G), R62.1
unnamed: C30.1, Q10.1 (G), R72.1
unnamed: R19.1, U6.1
unnamed: R21.2, R22.2, U6.4
unnamed: R25.1, U7.1
unnamed: R26.2, R27.2, U7.4
unnamed: R30.1, U8.1
unnamed: R31.2, R32.2, U8.4
unnamed: R35.1, U9.1
unnamed: R36.2, R37.2, U9.4
unnamed: R40.1, U10.1
unnamed: R41.2, R42.2, U10.4
unnamed: R45.1, U11.1
unnamed: R46.2, R47.2, U11.4
unnamed: R50.1, U12.1
unnamed: R51.2, R52.2, U12.4
unnamed: R55.1, U13.1
unnamed: R56.2, R57.2, U13.4
unnamed: R60.1, U14.1
unnamed: R61.2, R62.2, U14.4
unnamed: R70.1, U15.1
unnamed: R71.2, R72.2, U15.4
unnamed: R2.2, U1.44 (BOOT0)
unnamed: C5.1, R1.2, SW1.1, U1.7 (NRST)
unnamed: C8.2, U1.3 (PC14)
unnamed: C9.2, U1.4 (PC15)
unnamed: C6.2, U1.5 (PD0)
unnamed: C7.2, U1.6 (PD1)
unnamed: R5.2, U1.1 (VBAT)

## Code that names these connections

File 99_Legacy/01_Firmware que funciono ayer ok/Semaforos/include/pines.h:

// ===== include/pines.h =====
#pragma once

// --- Semáforo 1 (vehicular principal) ---
#define ROJO1       PA0   // S1 -> J3
#define AMARILLO1   PA1   // S2 -> J4
#define VERDE1      PA2   // S3 -> J5

// --- Semáforo 2 (vehicular secundario) ---
#define ROJO2       PA3   // S4 -> J6
#define AMARILLO2   PA4   // S5 -> J7
#define VERDE2      PA5   // S6 -> J8

// --- Semáforo peatonal ---
#define ROJO_PEATON   PA6 // S7 -> J11
#define VERDE_PEATON  PA7 // S8 -> J9

// --- Actuadores ---
#define LORA_DE_RE        PB12 // Control DE/~RE del MAX3485 (bus OUT) -> E90-DTU LoRa
                                // CORREGIDO: la PCB real tiene DE/~RE en PB12, no en PB0.
                                // PB0 está en el net "/Puerta", sin relación con el radio.
#define BUZZER             PB1  // J13 (19)
#define MOTOR_TALANQUERA   PB2  // J15 (20)

// --- LCD ST7920 (modo serial, 3 hilos + PSB + RST) ---
#define LCD_SCLK    PB3   // -> E del LCD  (clock serial)
#define LCD_CS      PB4   // -> RS del LCD (chip select)
#define LCD_SID     PB5   // -> RW del LCD (dato serial)
#define LCD_PSB     PB6   // -> PSB del LCD (fijo LOW)
#define LCD_RST     PB7   // -> RST del LCD (reset)

// --- Botones ---
#define BOTON1      PB9   // Arriba
#define BOTON2      PB13  // Abajo
#define BOTON3      PB14  // Aceptar
#define BOTON4      PB15  // Cancelar

// --- RS485 "IN" (USART1) ---
#define RS485_IN_RX     PA10
#define RS485_IN_TX     PA9
#define RS485_IN_DE_RE  PA8

// --- RS485 "OUT" (USART3) ---
#define RS485_OUT_RX    PB11
#define RS485_OUT_TX    PB10
// DE/RE is controlled by LORA_DE_RE (PB12) as defined above.
